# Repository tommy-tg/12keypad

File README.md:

# 12keypad
12 keys programmable Macropad based on RP2040 MCU from Raspberry Pi, running [KMK firmware](https://github.com/KMKfw/kmk_firmware)

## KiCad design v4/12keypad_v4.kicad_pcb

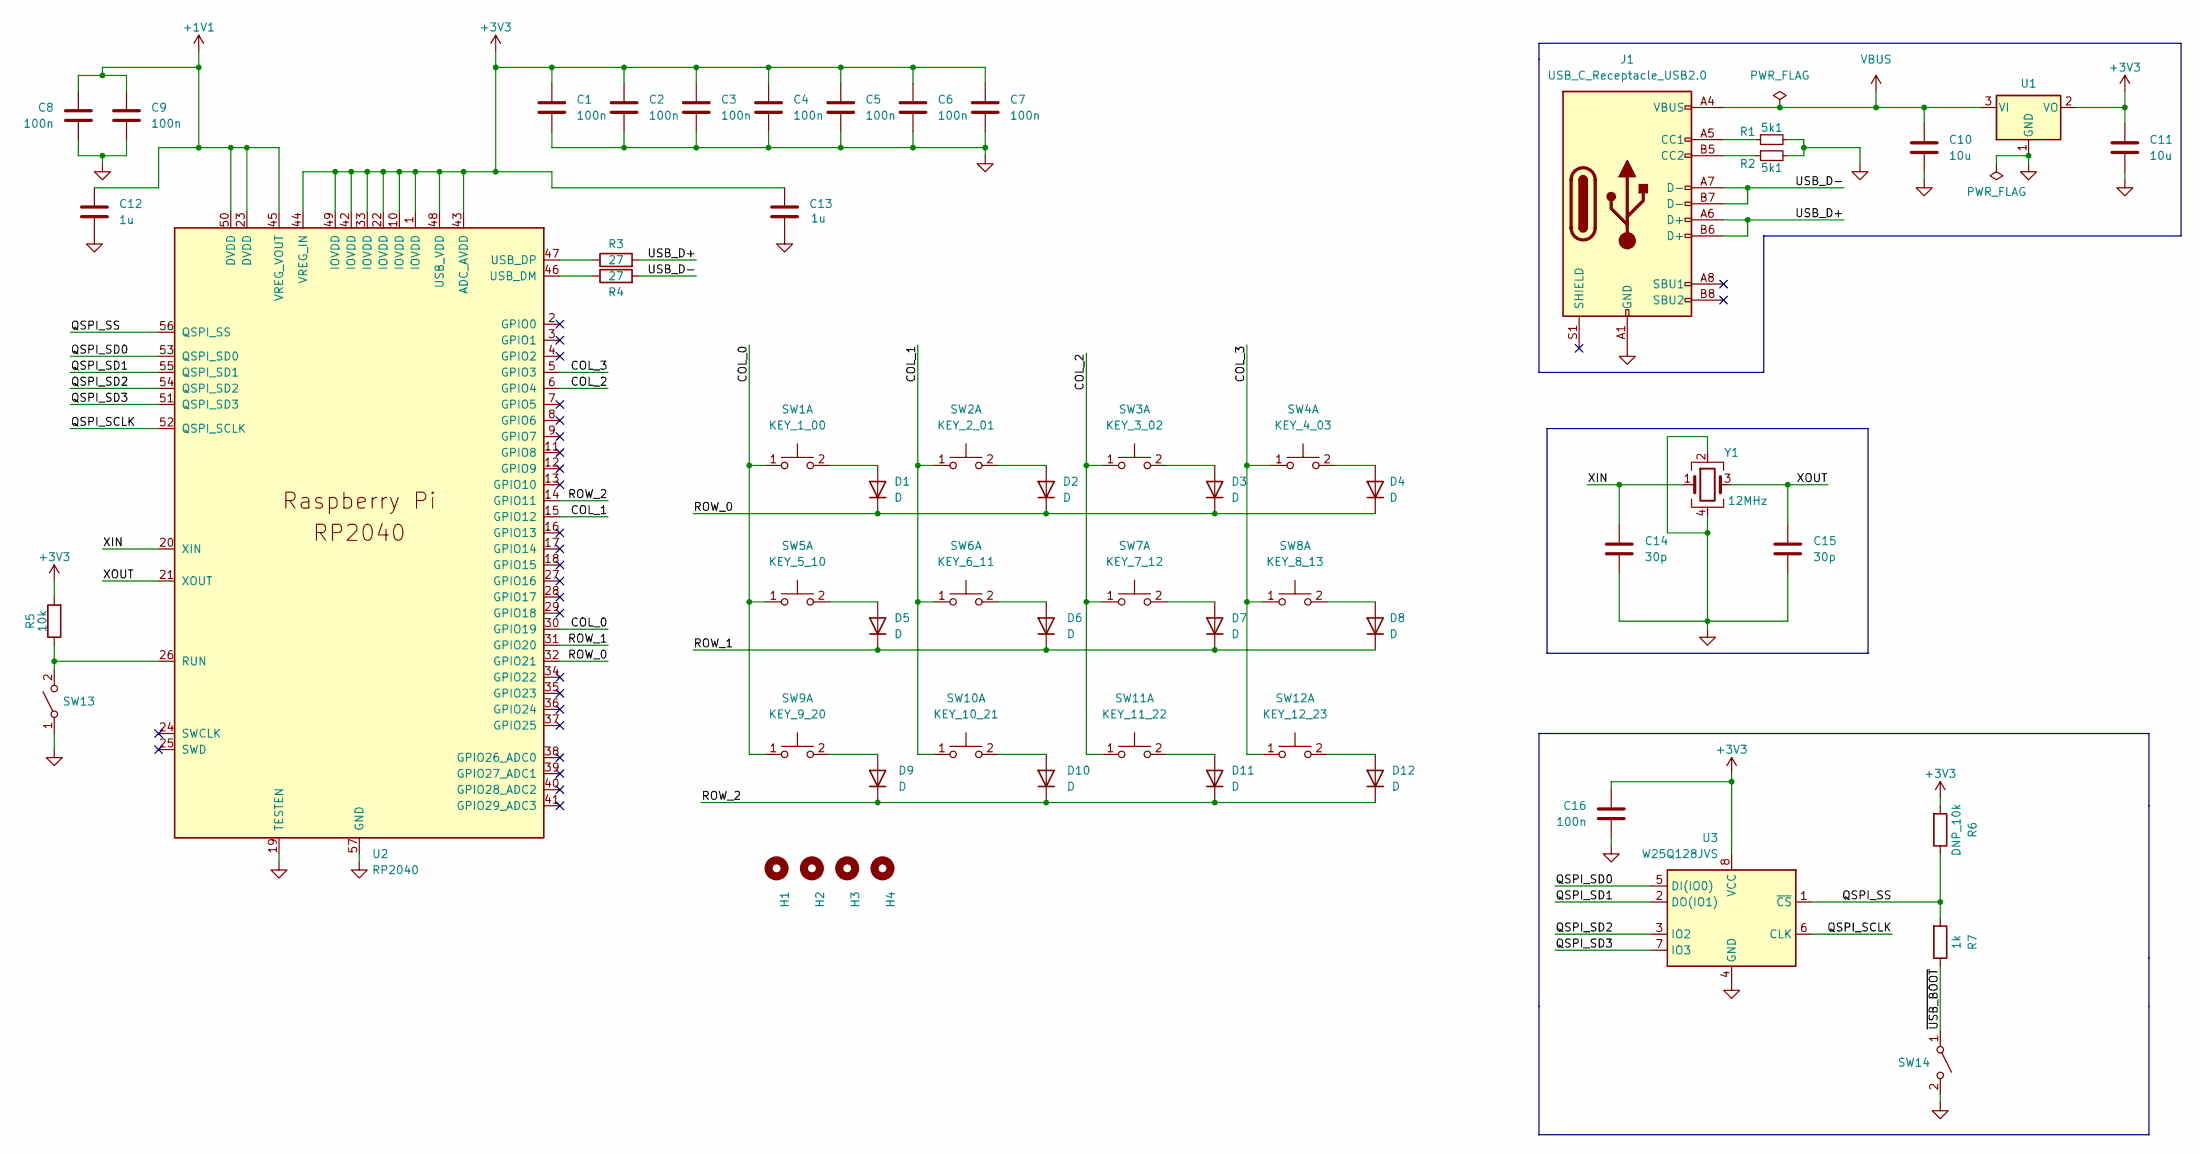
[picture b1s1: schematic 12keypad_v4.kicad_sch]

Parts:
C1, C2, C3, C4, C5, C6, C7, C8, C9, C16: 100n; C_0402_1005Metric
C10, C11: 10u; C_0603_1608Metric
C12, C13: 1u; C_0402_1005Metric
C14, C15: 30p; C_0402_1005Metric
D1, D2, D3, D4, D5, D6, D7, D8, D9, D10, D11, D12: D; D_SOD-123
H1, H2, H3, H4: MountingHole; MountingHole_2.2mm_M2
J1: USB_C_Receptacle_USB2.0; USB_C_Receptacle_XKB_U262-16XN-4BVC11
R1, R2: 5k1; R_0402_1005Metric
R3, R4: 27; R_0603_1608Metric
R5: 10k; R_0402_1005Metric
R6: DNP_10k; R_0402_1005Metric
R7: 1k; R_0402_1005Metric
SW1: KEY_1_00; SW_Cherry_MX_1.00u_PCB_UPDATED_FOOTPRINT_RIGHT_PIN_ASSIGNME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
SW2: KEY_2_01; SW_Cherry_MX_1.00u_PCB_UPDATED_FOOTPRINT_RIGHT_PIN_ASSIGNME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
SW3: KEY_3_02; SW_Cherry_MX_1.00u_PCB_UPDATED_FOOTPRINT_RIGHT_PIN_ASSIGNME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
SW4: KEY_4_03; SW_Cherry_MX_1.00u_PCB_UPDATED_FOOTPRINT_RIGHT_PIN_ASSIGNME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
SW5: KEY_5_10; SW_Cherry_MX_1.00u_PCB_UPDATED_FOOTPRINT_RIGHT_PIN_ASSIGNME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
SW6: KEY_6_11; SW_Cherry_MX_1.00u_PCB_UPDATED_FOOTPRINT_RIGHT_PIN_ASSIGNME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
SW7: KEY_7_12; SW_Cherry_MX_1.00u_PCB_UPDATED_FOOTPRINT_RIGHT_PIN_ASSIGNME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
SW8: KEY_8_13; SW_Cherry_MX_1.00u_PCB_UPDATED_FOOTPRINT_RIGHT_PIN_ASSIGNME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
SW9: KEY_9_20; SW_Cherry_MX_1.00u_PCB_UPDATED_FOOTPRINT_RIGHT_PIN_ASSIGNME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
SW10: KEY_10_21; SW_Cherry_MX_1.00u_PCB_UPDATED_FOOTPRINT_RIGHT_PIN_ASSIGNME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
SW11: KEY_11_22; SW_Cherry_MX_1.00u_PCB_UPDATED_FOOTPRINT_RIGHT_PIN_ASSIGNME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
SW12: KEY_12_23; SW_Cherry_MX_1.00u_PCB_UPDATED_FOOTPRINT_RIGHT_PIN_ASSIGNME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
SW13, SW14: SW_SPST; SW_Push_1P1T_XKB_TS-1187A
U1: NCP1117-3.3_SOT223; SOT-223-3_TabPin2
U2: RP2040; RP2040-QFN-56
U3: W25Q128JVS; SOIC-8_5.23x5.23mm_P1.27mm
Y1: 12MHz; Crystal_SMD_3225-4Pin_3.2x2.5mm

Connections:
+1V1: C8.2, C9.1, C12.1, U2.23 (DVDD), U2.45 (VREG_VOUT), U2.50 (DVDD)
+3V3: C1.1, C2.1, C3.1, C4.1, C5.1, C6.1, C7.1, C11.1, C13.1, C16.1, R5.2, R6.2, U1.2 (VO), U2.1 (IOVDD), U2.10 (IOVDD), U2.22 (IOVDD), U2.33 (IOVDD), U2.42 (IOVDD), U2.43 (ADC_AVDD), U2.44 (VREG_IN), U2.48 (USB_VDD), U2.49 (IOVDD), U3.8 (VCC)
/COL_0: SW1.1, SW5.1, SW9.1, U2.30 (GPIO19)
/COL_1: SW2.1, SW6.1, SW10.1, U2.15 (GPIO12)
/COL_2: SW3.1, SW7.1, SW11.1, U2.6 (GPIO4)
/COL_3: SW4.1, SW8.1, SW12.1, U2.5 (GPIO3)
/QSPI_SCLK: U2.52 (QSPI_SCLK), U3.6 (CLK)
/QSPI_SD0: U2.53 (QSPI_SD0), U3.5 (DI(IO0))
/QSPI_SD1: U2.55 (QSPI_SD1), U3.2 (DO(IO1))
/QSPI_SD2: U2.54 (QSPI_SD2), U3.3 (IO2)
/QSPI_SD3: U2.51 (QSPI_SD3), U3.7 (IO3)
/QSPI_SS: R6.1, R7.2, U2.56 (QSPI_SS), U3.1 (~CS)
/ROW_0: D1.1 (K), D2.1 (K), D3.1 (K), D4.1 (K), U2.32 (GPIO21)
/ROW_1: D5.1 (K), D6.1 (K), D7.1 (K), D8.1 (K), U2.31 (GPIO20)
/ROW_2: D9.1 (K), D10.1 (K), D11.1 (K), D12.1 (K), U2.14 (GPIO11)
/USB_D+: J1.A6 (D+), J1.B6 (D+), R3.2
/USB_D-: J1.A7 (D-), J1.B7 (D-), R4.2
/XIN: C14.1, U2.20 (XIN), Y1.1
/XOUT: C15.1, U2.21 (XOUT), Y1.3
/~USB_BOOT: R7.1, SW14.1 (A)
GND: C1.2, C2.2, C3.2, C4.2, C5.2, C6.2, C7.2, C8.1, C9.2, C10.2, C11.2, C12.2, C13.2, C14.2, C15.2, C16.2, J1.A1 (GND), J1.A12 (GND), J1.B1 (GND), J1.B12 (GND), R1.2, R2.2, SW13.1 (A), SW14.2 (B), U1.1 (GND), U2.19 (TESTEN), U2.57 (GND), U3.4 (GND), Y1.2, Y1.4
unnamed: D1.2 (A), SW1.2
unnamed: D2.2 (A), SW2.2
unnamed: D3.2 (A), SW3.2
unnamed: D4.2 (A), SW4.2
unnamed: D5.2 (A), SW5.2
unnamed: D6.2 (A), SW6.2
unnamed: D7.2 (A), SW7.2
unnamed: D8.2 (A), SW8.2
unnamed: D9.2 (A), SW9.2
unnamed: D10.2 (A), SW10.2
unnamed: D11.2 (A), SW11.2
unnamed: D12.2 (A), SW12.2
unnamed: J1.A5 (CC1), R1.1
unnamed: J1.B5 (CC2), R2.1
unnamed: R5.1, SW13.2 (B), U2.26 (RUN)
unnamed: R4.1, U2.46 (USB_DM)
unnamed: R3.1, U2.47 (USB_DP)
VBUS: C10.1, J1.A4 (VBUS), J1.A9 (VBUS), J1.B4 (VBUS), J1.B9 (VBUS), U1.3 (VI)

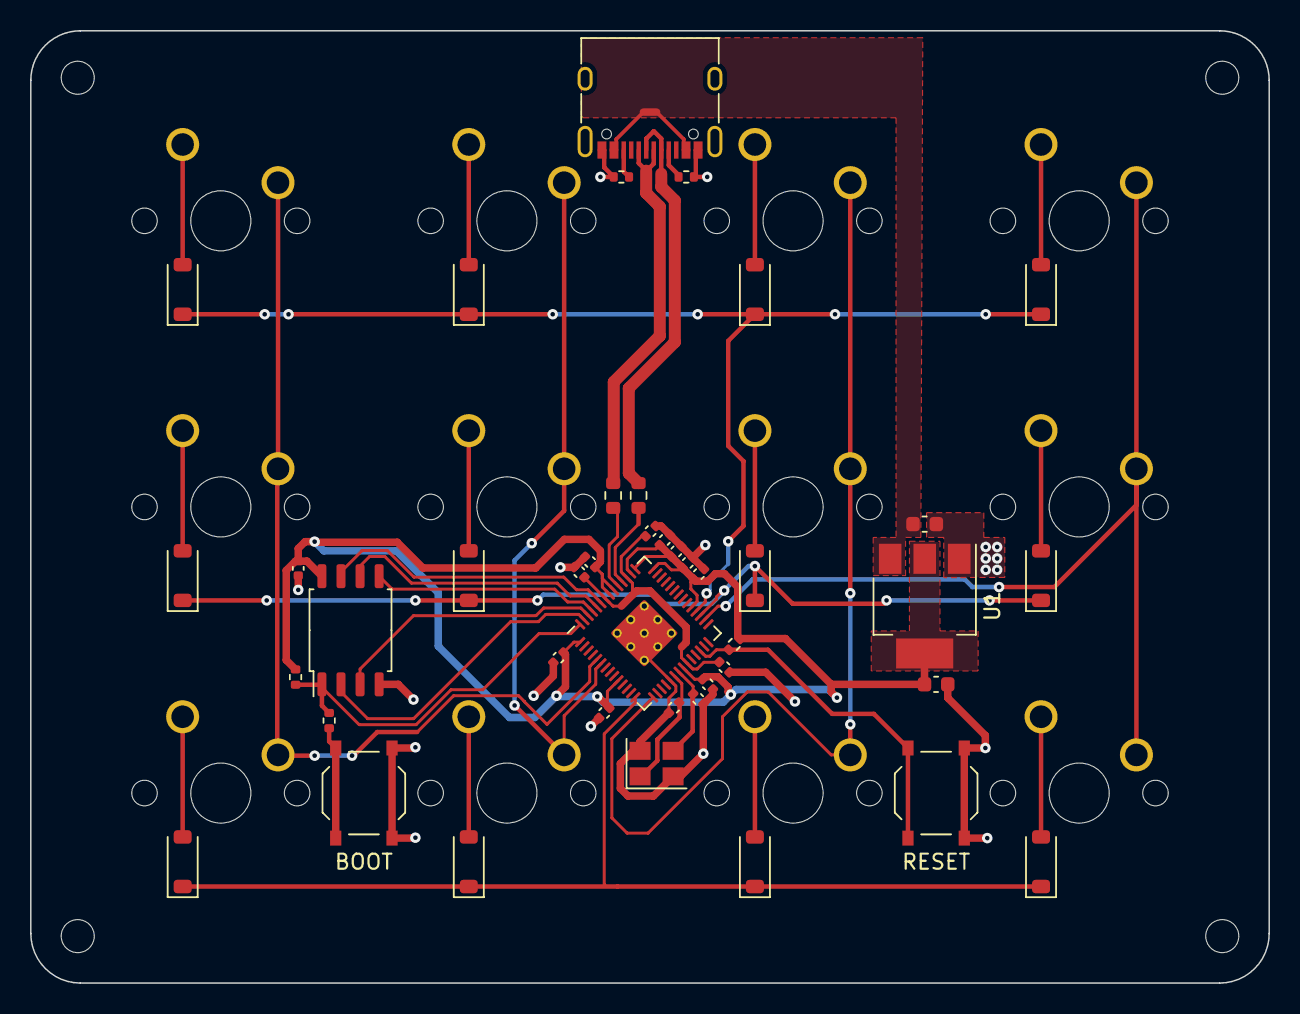
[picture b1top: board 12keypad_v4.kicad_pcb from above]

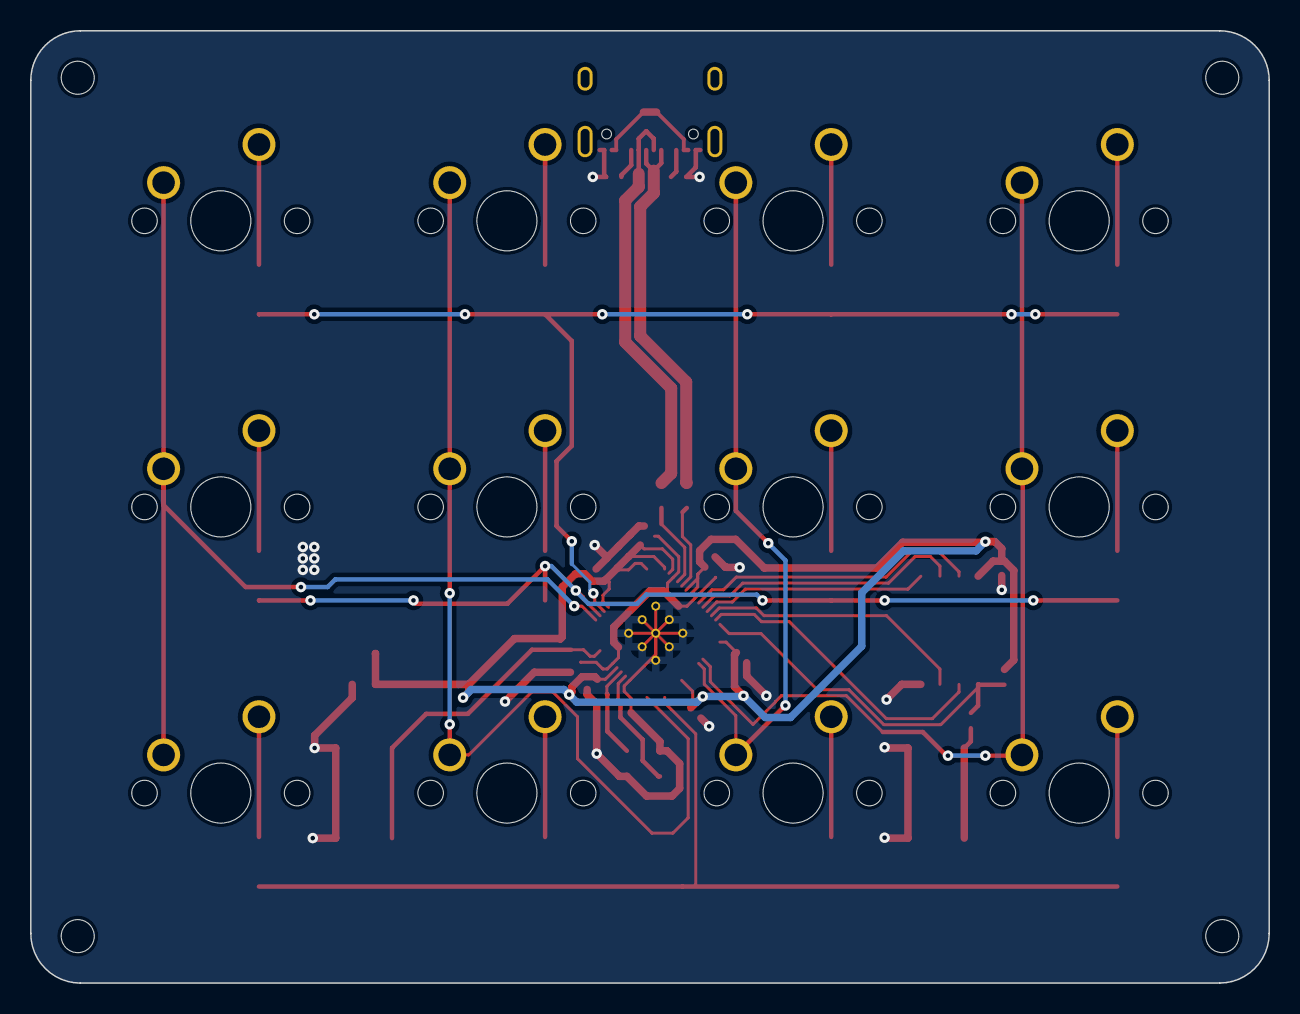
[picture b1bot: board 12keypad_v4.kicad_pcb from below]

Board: 2 copper layers, 82.5 x 63.4 mm, 58 parts (12 on the bottom side), 39 nets.

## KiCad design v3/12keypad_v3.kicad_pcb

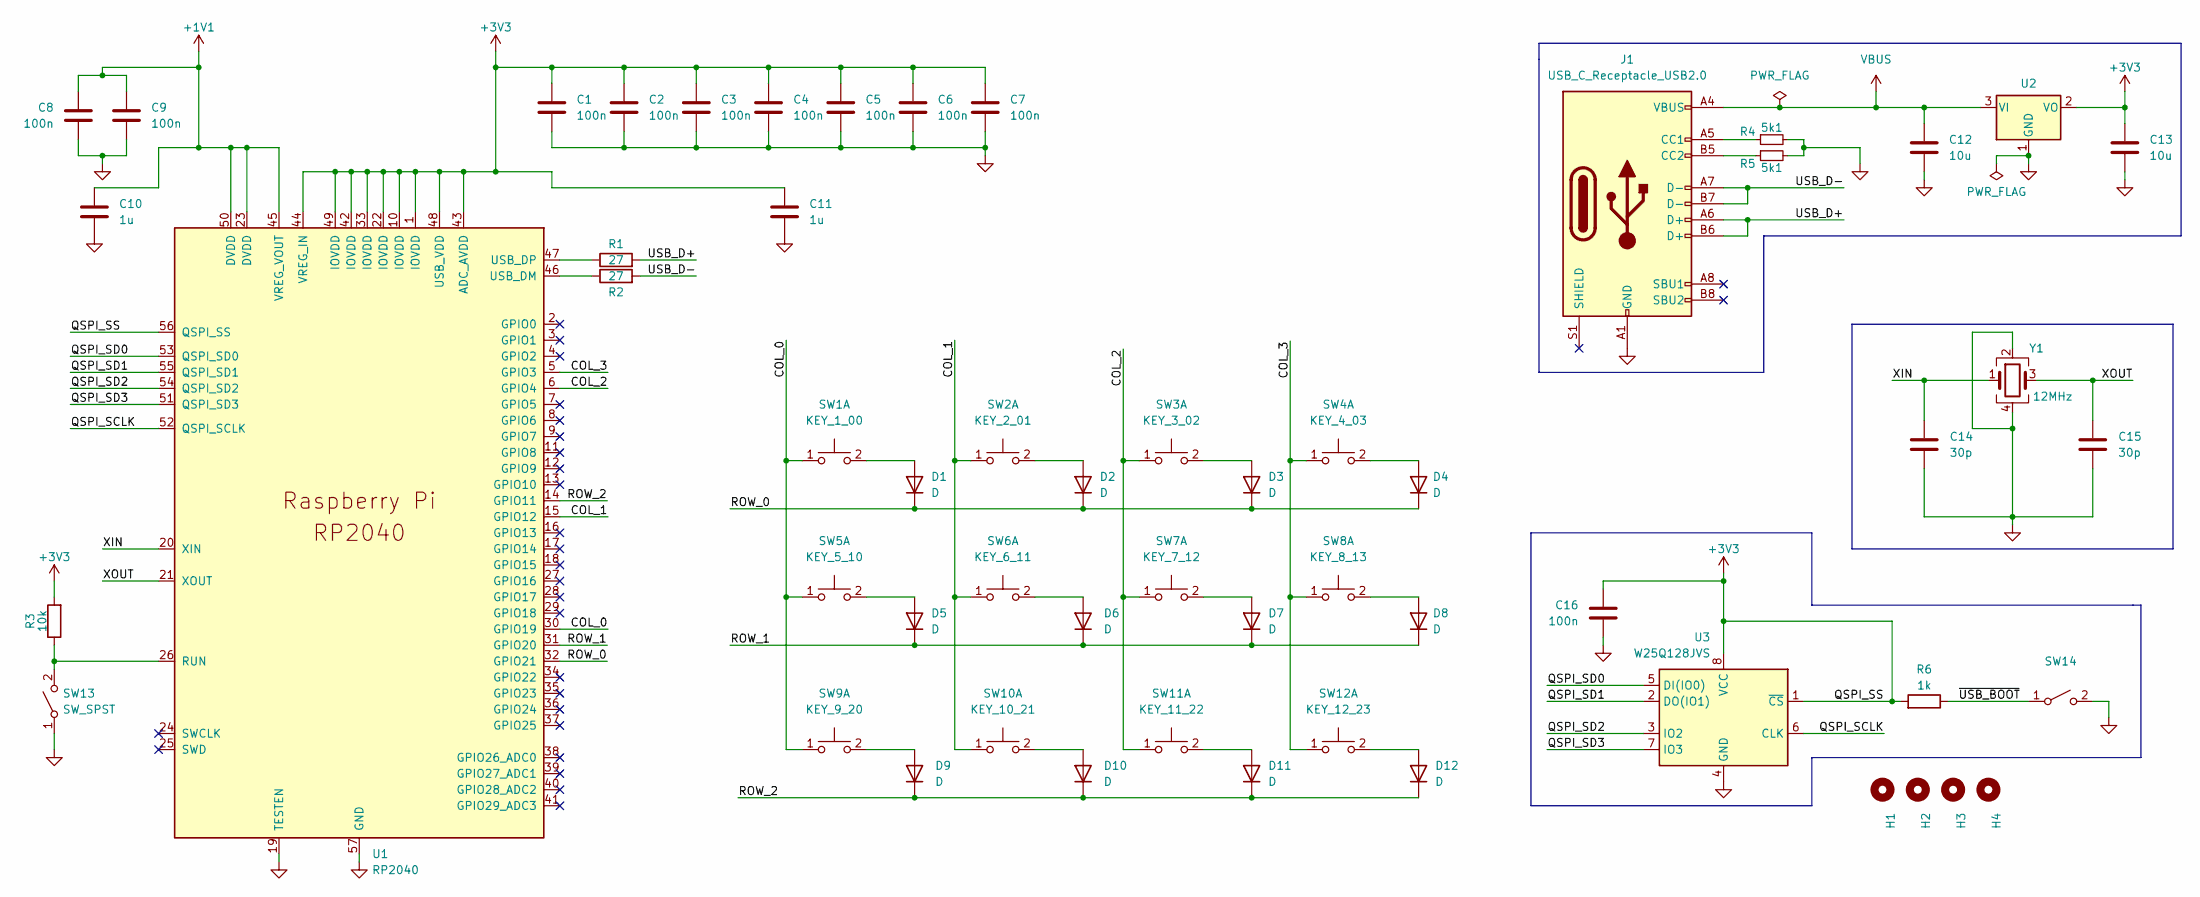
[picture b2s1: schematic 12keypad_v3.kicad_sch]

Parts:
C1, C2, C3, C4, C5, C6, C7, C8, C9, C16: 100n; C_0402_1005Metric
C10, C11: 1u; C_0402_1005Metric
C12, C13: 10u; C_0603_1608Metric
C14, C15: 30p; C_0402_1005Metric
D1, D2, D3, D4, D5, D6, D7, D8, D9, D10, D11, D12: D; D_SOD-123
H1, H2, H3, H4: MountingHole; MountingHole_2.2mm_M2
J1: USB_C_Receptacle_USB2.0; USB_C_Receptacle_XKB_U262-16XN-4BVC11
R1, R2: 27; R_0603_1608Metric
R3: 10k; R_0402_1005Metric
R4, R5: 5k1; R_0402_1005Metric
R6: 1k; R_0402_1005Metric
SW1: KEY_1_00; SW_Cherry_MX_1.00u_PCB
SW2: KEY_2_01; SW_Cherry_MX_1.00u_PCB
SW3: KEY_3_02; SW_Cherry_MX_1.00u_PCB
SW4: KEY_4_03; SW_Cherry_MX_1.00u_PCB
SW5: KEY_5_10; SW_Cherry_MX_1.00u_PCB
SW6: KEY_6_11; SW_Cherry_MX_1.00u_PCB
SW7: KEY_7_12; SW_Cherry_MX_1.00u_PCB
SW8: KEY_8_13; SW_Cherry_MX_1.00u_PCB
SW9: KEY_9_20; SW_Cherry_MX_1.00u_PCB
SW10: KEY_10_21; SW_Cherry_MX_1.00u_PCB
SW11: KEY_11_22; SW_Cherry_MX_1.00u_PCB
SW12: KEY_12_23; SW_Cherry_MX_1.00u_PCB
SW13, SW14: SW_SPST; SW_Push_1P1T_XKB_TS-1187A
U1: RP2040; RP2040-QFN-56
U2: NCP1117-3.3_SOT223; SOT-223-3_TabPin2
U3: W25Q128JVS; SOIC-8_5.23x5.23mm_P1.27mm
Y1: 12MHz; Crystal_SMD_3225-4Pin_3.2x2.5mm

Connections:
+1V1: C8.2, C9.1, C10.1, U1.23 (DVDD), U1.45 (VREG_VOUT), U1.50 (DVDD)
+3V3: C1.1, C2.1, C3.1, C4.1, C5.1, C6.1, C7.1, C11.1, C13.1, C16.1, R3.2, R6.2, U1.1 (IOVDD), U1.10 (IOVDD), U1.22 (IOVDD), U1.33 (IOVDD), U1.42 (IOVDD), U1.43 (ADC_AVDD), U1.44 (VREG_IN), U1.48 (USB_VDD), U1.49 (IOVDD), U1.56 (QSPI_SS), U2.2 (VO), U3.1 (~CS), U3.8 (VCC)
/COL_0: SW1.1, SW5.1, SW9.1, U1.30 (GPIO19)
/COL_1: SW2.1, SW6.1, SW10.1, U1.15 (GPIO12)
/COL_2: SW3.1, SW7.1, SW11.1, U1.6 (GPIO4)
/COL_3: SW4.1, SW8.1, SW12.1, U1.5 (GPIO3)
/QSPI_SCLK: U1.52 (QSPI_SCLK), U3.6 (CLK)
/QSPI_SD0: U1.53 (QSPI_SD0), U3.5 (DI(IO0))
/QSPI_SD1: U1.55 (QSPI_SD1), U3.2 (DO(IO1))
/QSPI_SD2: U1.54 (QSPI_SD2), U3.3 (IO2)
/QSPI_SD3: U1.51 (QSPI_SD3), U3.7 (IO3)
/ROW_0: D1.1 (K), D2.1 (K), D3.1 (K), D4.1 (K), U1.32 (GPIO21)
/ROW_1: D5.1 (K), D6.1 (K), D7.1 (K), D8.1 (K), U1.31 (GPIO20)
/ROW_2: D9.1 (K), D10.1 (K), D11.1 (K), D12.1 (K), U1.14 (GPIO11)
/USB_D+: J1.A6 (D+), J1.B6 (D+), R1.2
/USB_D-: J1.A7 (D-), J1.B7 (D-), R2.2
/XIN: C14.1, U1.20 (XIN), Y1.1
/XOUT: C15.1, U1.21 (XOUT), Y1.3
/~USB_BOOT: R6.1, SW14.1 (A)
GND: C1.2, C2.2, C3.2, C4.2, C5.2, C6.2, C7.2, C8.1, C9.2, C10.2, C11.2, C12.2, C13.2, C14.2, C15.2, C16.2, J1.A1 (GND), J1.A12 (GND), J1.B1 (GND), J1.B12 (GND), R4.2, R5.2, SW13.1 (A), SW14.2 (B), U1.19 (TESTEN), U1.57 (GND), U2.1 (GND), U3.4 (GND), Y1.2, Y1.4
unnamed: D1.2 (A), SW1.2
unnamed: D2.2 (A), SW2.2
unnamed: D3.2 (A), SW3.2
unnamed: D4.2 (A), SW4.2
unnamed: D5.2 (A), SW5.2
unnamed: D6.2 (A), SW6.2
unnamed: D7.2 (A), SW7.2
unnamed: D8.2 (A), SW8.2
unnamed: D9.2 (A), SW9.2
unnamed: D10.2 (A), SW10.2
unnamed: D11.2 (A), SW11.2
unnamed: D12.2 (A), SW12.2
unnamed: J1.A5 (CC1), R4.1
unnamed: J1.B5 (CC2), R5.1
unnamed: R3.1, SW13.2 (B), U1.26 (RUN)
unnamed: R2.1, U1.46 (USB_DM)
unnamed: R1.1, U1.47 (USB_DP)
VBUS: C12.1, J1.A4 (VBUS), J1.A9 (VBUS), J1.B4 (VBUS), J1.B9 (VBUS), U2.3 (VI)

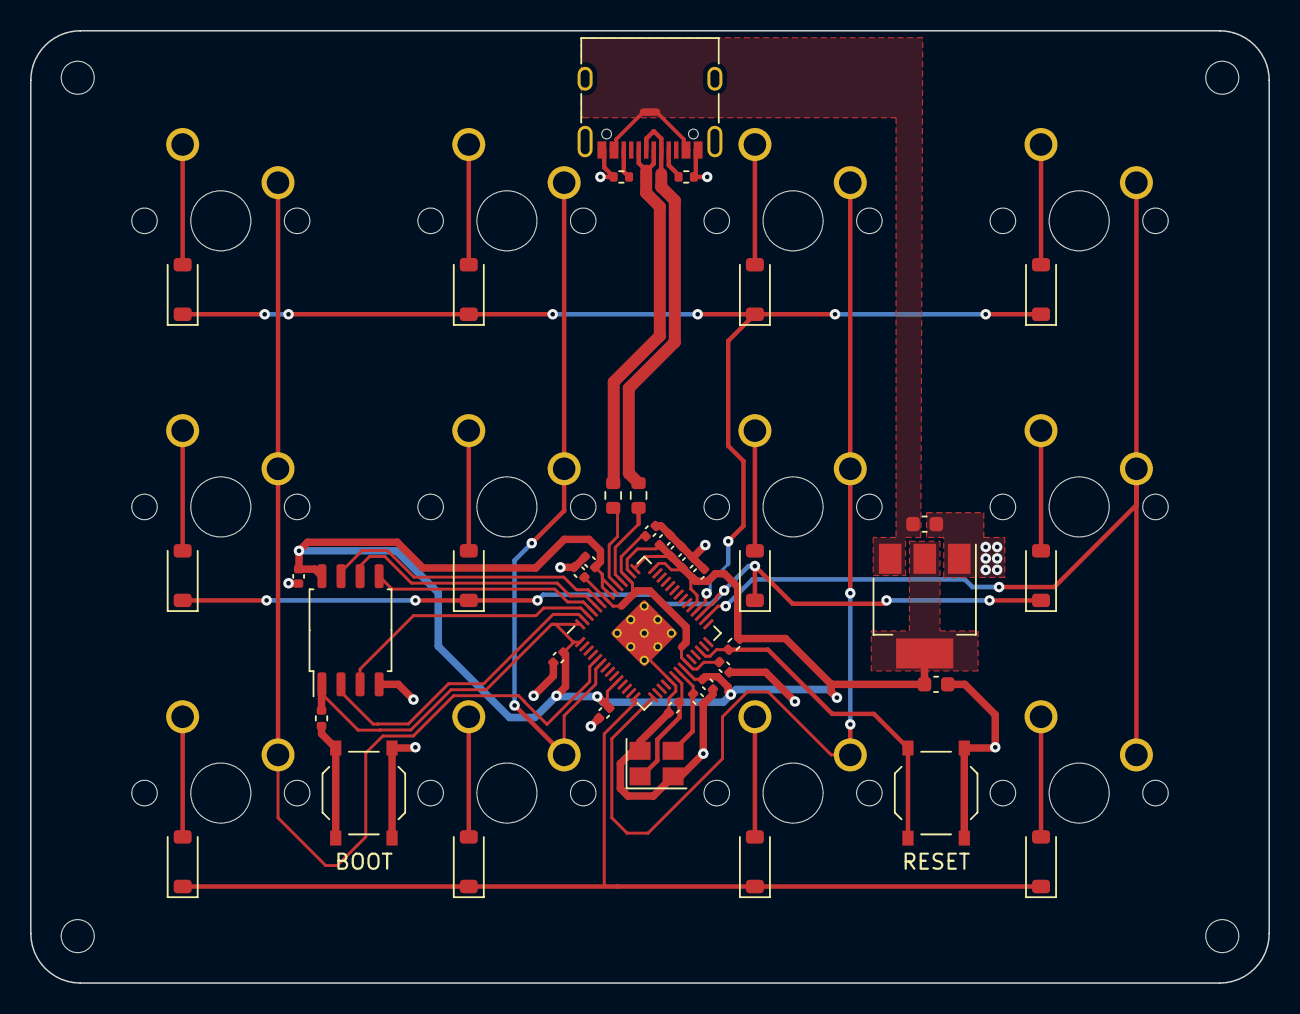
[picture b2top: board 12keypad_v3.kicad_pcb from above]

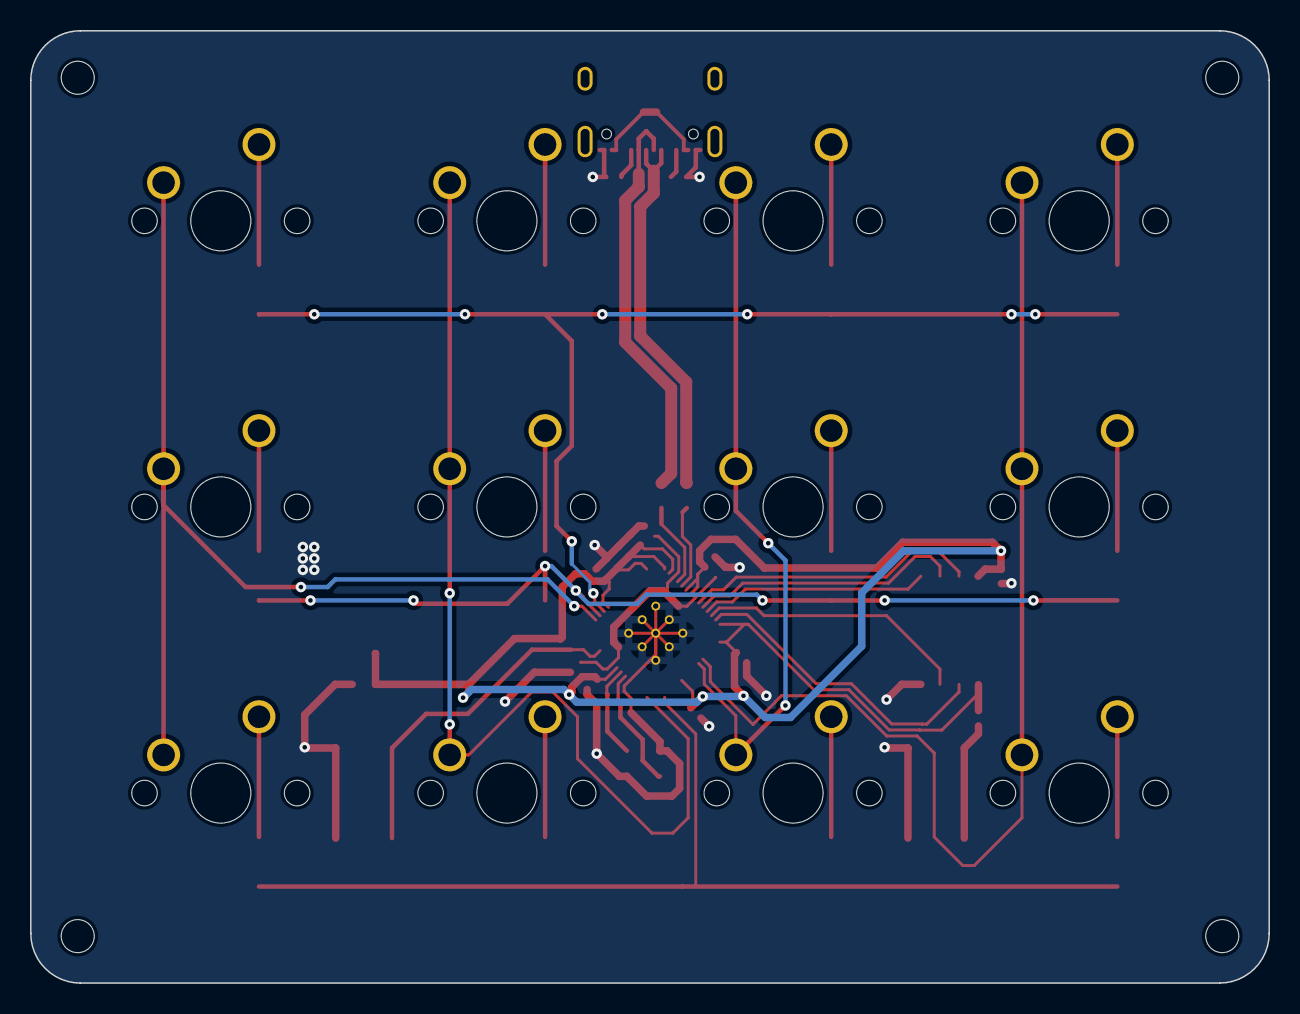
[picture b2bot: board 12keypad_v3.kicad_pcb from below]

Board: 2 copper layers, 82.5 x 63.4 mm, 57 parts (12 on the bottom side), 38 nets.

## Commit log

2023-01-13 first commit, add v0.1 of rp2040 kicad project
2023-01-13 .gitignore update
2023-01-13 add README.md file
2023-01-13 gitignore update
2023-01-16 center of usb c port
2023-01-16 add rev1.0 and 5x5rev0.1
2023-01-16 update git ignore
2023-01-24 update gitignore
2023-01-24 update pcb layout
2023-02-19 add complete v1.0
2023-02-19 v2.0 add
2023-02-19 general commit
2023-10-14 add v3 source files
2023-10-14 add v4 source files
2023-10-14 add pcb render
2023-10-14 add LICENSE
2023-10-14 add assembled and kit photos
2023-10-14 add assembled photo
2023-10-14 remove assembled photo
